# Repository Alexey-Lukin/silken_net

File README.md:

# 🌿 Silken Net

> ⚠️ **2026-11-22 — the project is being re-rooted.** The enzymatic fuel cell (EBFC) is cut from the product; hardware is to be designed for sampled «witness trees» rather than every tree, and a primary cell is now an allowed power source; the core product direction is an open radio dendrometer for research groups, with a second market and a sensor-agnostic node under study; the planned in-silico EBFC paper («Стаття 1») will not be published. Everything below still describes the previous design until it is rewritten. The verdicts live in [`docs/01_03_EBFC_Enzymatic_Bio_Fuel_Cell.md`](docs/01_03_EBFC_Enzymatic_Bio_Fuel_Cell.md) (§4, first paragraph), [`docs/00_01_Vision_Mission_and_Roadmap.md`](docs/00_01_Vision_Mission_and_Roadmap.md) (§2) and [`docs/00_02_Academic_Integration_and_IP.md`](docs/00_02_Academic_Integration_and_IP.md) (§2.1).

<!-- hero: one representative per macro-layer, bottom-up (tree → blockchain) -->
<p align="center">
  <a href="docs/01_03_EBFC_Enzymatic_Bio_Fuel_Cell.md">500mV in silico" src="https://img.shields.io/badge/EBFC%20%3E500mV%20in%20silico-2E7D32?style=flat-square"></a>

</p>

**Silken Net** is the world's first trustless **D-MRV** (Digital Measurement, Reporting & Verification) platform for planetary-scale forest-health monitoring. Each tree gets a machine identity (peaq DID), becomes an economic agent, and earns growth points that convert to **SCC** — computed from the node's wake interval (by design, its fuel cell's recharge time), a transitional rule until a separate growth witness exists; SCC is an internal accounting unit, not a registry carbon credit.

A titanium gyroid anchor carries an STM32 *Soldier* node whose power source is an open research bet — an enzymatic biofuel cell built into the anchor (EBFC, >500 mV computed in silico, not yet measured in a tree). The node senses → encrypts → transmits over LoRa 868 MHz to a *Queen* gateway, which relays via CoAP to a Rails 8 / PostgreSQL / Sidekiq backend and a 10-chain Web3 *Proof-of-Growth* pipeline.

> *"We do not merely watch the forest. We give it a digital will."*

**A note on language.** This README, [`CONTRIBUTING.md`](CONTRIBUTING.md) and [`SECURITY.md`](SECURITY.md) are in English; the `docs/` canon is written in Ukrainian, because it is where the engineering thinking actually happens and translating it would put a lossy layer between the author and the decisions. Issues and pull requests in English are welcome.

---

## 📚 Documentation

The canon lives in [`docs/`](docs/) as SSOT documents grouped into modules 00–06, and is mirrored to the GitHub wiki on every push to `main`.

> **Start at [`docs/00_00` — SSOT Index](docs/00_00_SSOT_Index.md):** reading order, the eight-layer system map, and a one-line description of every document. That index is the **single home of the list** — it is deliberately not restated here, so it cannot drift in two places.

- **Module 00 — foundation** (read first): vision and roadmap · AI-native method and NASA TRL · the TRL matrix with HIL simulators · the SSOT documentation standard · academic integration and the IP posture · Nature-as-a-Service contract terms · the beyond-TRL-9 agenda
- **Modules 01–06 — the system:** anchor and biofuel cell · capsule and gateway hardware (with the unit economics and BOM) · firmware and edge AI · the Rails core · Web3 and economics · deploy and observability

🔴 **Everything still unfinished — including the honest blockers — lives in [`docs/00_07` — Action Plan Tracker](docs/00_07_Action_Plan_Tracker.md).** It is a working document, not a highlight reel: open defects, refused proposals and named ceilings are in it on purpose.

---

## 🌍 The scale we build for

**One trillion trees.** Not "planetary" as a figure of speech — planetary as an order of magnitude: Earth carries roughly three trillion trees, and the design target is that any one of them can hold a machine identity, report on itself, and be paid for verified growth.

That number is a design constraint, not a boast. It is the denominator every architectural decision is divided by — RANGE-partitioned telemetry, strict-priority job queues, per-stream broadcast granularity, the bill of materials for a single node, the energy budget of a sensor that must run for two decades without a wire. A choice that is merely *fine* at ten thousand nodes and quietly quadratic at 10¹² is a defect here, even while it passes every test.

**And the honest half:** today the system stands at **TRL 3**, gated by the anchor and the biofuel cell — in-silico validated, not yet in-vitro; zero nodes in a forest. The trillion is what we are building *toward* and measuring *against*, never a claim about what runs today. This section is the public rendering; the canonical home of the constraint is [`docs/00_01 §1.1`](docs/00_01_Vision_Mission_and_Roadmap.md), which is where the rest of the canon cites the 10¹² denominator from. Current per-module readiness lives in [`docs/00_03 §1`](docs/00_03_TRL_Matrix_HIL_and_Beyond.md); the scaling phases and the beyond-TRL-9 agenda both in [`docs/00_01 §4`](docs/00_01_Vision_Mission_and_Roadmap.md).

---

## 🧬 Technology stack — a vertical cut through the trunk

_Bottom-up, the way sap climbs the xylem: from the root inside a living tree (**L1**) to finalisation on Ethereum (**L8**). What each layer means and what gates it — [`docs/00_00` § System Map](docs/00_00_SSOT_Index.md); the current readiness of each module — [`docs/00_03 §1`](docs/00_03_TRL_Matrix_HIL_and_Beyond.md), its single home, deliberately not restated here._

| Layer | Stack |
|:---|:---|
| **L1 · ROOT**<br><sub>Biophysics</sub> |         |
| **L2 · CAPSULE**<br><sub>Hardware</sub> |      |
| **L3 · BRAIN**<br><sub>Firmware + edge AI</sub> |        |
| **L4 · VESSELS**<br><sub>Network</sub> |     |
| **L5 · HEARTWOOD**<br><sub>Backend</sub> |             |
| ⛓ **L6 · CAMBIUM**<br><sub>Verification</sub> |      |
| ⛓ **L7 · CROWN**<br><sub>Finance</sub> |        |
| ⛓ **L8 · CANOPY TOP**<br><sub>Finalisation</sub> |     |
| 🌍 **SOIL**<br><sub>DevOps · CI · observability</sub> |                |

---

## 🚀 Quick start

### 0. System dependencies

Install these before `bundle install`.

**PostGIS** (required — cluster geometry lives in the database):

```bash
sudo apt-get install -y postgresql-17-postgis-3 postgresql-17-postgis-3-scripts   # Ubuntu / Debian
brew install postgis                                                             # macOS
```

The extension is enabled by `structure.sql` (`CREATE EXTENSION IF NOT EXISTS postgis`), so a normal `db:prepare` needs no manual step.

**A C toolchain** — several gems compile native extensions on install (e.g. `rbsecp256k1` builds libsecp256k1; `ed25519`, `keccak`, `oj`, `pg_query`, `puma`):

```bash
sudo apt-get install -y build-essential ruby-dev   # Ubuntu / Debian
xcode-select --install                             # macOS
```

### 1. Clone and set up

```bash
git clone https://github.com/Alexey-Lukin/silken_net.git
cd silken_net
bundle install
bin/rails db:prepare
```

### 2. Environment (`.env`)

```bash
cp .env.example .env
```

For local development and simulated telemetry most fields can stay empty — `REDIS_URL` (already in the template) and `WEB3_STRICT_MODE=false` are enough, the latter activating the Web3 stubs so no real keys are needed. Running the full Web3 stack (SCC minting, the Chainlink oracle, Solana micro-payments) needs real credentials; the inventory of which, and where each comes from, is [`docs/06_04` — Secrets Checklist](docs/06_04_Secrets_Checklist.md).

### 3. Run

```bash
bin/dev   # Rails + Sidekiq + Tailwind CSS + CoAP listener
```

### 4. Simulate telemetry (no physical hardware)

```bash
bin/rails runner "PartitionMaintenanceWorker.new.perform"   # partitions FIRST — see note
bin/rails db:seed      # Gateway, Tree, HardwareKey, TreeFamily
bin/forest_simulator   # CoAP packets from 5–15 Soldiers every 3–8 s
```

> **Why the worker runs first.** `db/seeds.rb` back-dates the "silent tree" to
> `73.hours.ago`, so on the 1st–3rd of a month that row targets the PREVIOUS month.
> `db/structure.sql` only carries the calendar frozen at dump time — if that month is
> missing, the row lands in the `_default` leaf silently and then blocks
> `CREATE … PARTITION OF` for it permanently (runbook `docs/06_06` §5.5). On
> `production` the seed refuses to run at all (slot guard; `00_07` OPS.38).

Watch the pipeline:

```bash
bin/rails runner "puts TelemetryLog.count"
open http://localhost:3000/sidekiq
tail -f log/development.log | grep -i telemetry
```

### 5. Tests and quality

```bash
bin/rspec                # full suite
bin/rubocop -a           # linter, safe autocorrect — run before every commit
bin/brakeman             # static security analysis
bin/bundler-audit check  # dependency advisories
```

Smart contracts (Foundry):

```bash
cd contracts
npm ci                           # OpenZeppelin + forge-std
forge build --sizes              # compile, report EIP-170 size
forge test -vvv --gas-report
forge coverage --report lcov     # ≥90% floor, enforced in CI
```

Suites live in `contracts/test/*.t.sol` — unit, symbolic proofs (Halmos + hevm), Medusa property fuzzing and Foundry stateful invariants. All of them gate merges into `main`.

### 6. Deploy (Kamal)

```bash
kamal setup
kamal deploy
```

> 🔏 **Signed releases.** The production image mirrored to GHCR carries a Sigstore-signed SLSA build-provenance attestation — verify it before pulling, per [`SECURITY.md`](SECURITY.md): `gh attestation verify oci://ghcr.io/alexey-lukin/silken_net:<tag> --owner Alexey-Lukin`.

---

## 🤝 Contributing

Bugs and proposals go through [GitHub Issues](https://github.com/Alexey-Lukin/silken_net/issues); vulnerabilities go **privately**, per [`SECURITY.md`](SECURITY.md) — please do not open a public issue for those. The contribution process (fork → branch → PR), the local checks to run before pushing, and the code requirements are in [`CONTRIBUTING.md`](CONTRIBUTING.md). Issues and pull requests in English are welcome even though the canon is Ukrainian.

---

## 📜 Licence and IP posture

SilkenNet is **mission-first and defensive-publication-first**: we deliberately **do not patent** this work. We publish it as prior art so that it stays free for every forest and **cannot be enclosed** by anyone — including us. The canonical statement of that posture is [`00_01 §8`](docs/00_01_Vision_Mission_and_Roadmap.md); the full map of zones and exceptions is [`NOTICE`](NOTICE).

| Zone | Licence | File |
|------|---------|------|
| **Code** (backend / firmware / tooling / IaC) | **GNU AGPL-3.0-or-later** — per-file SPDX | [`LICENSE`](LICENSE) |
| **Smart contracts** (`contracts/*.sol`) | **MIT** — per-file SPDX (on-chain composability and audit tooling) | [`LICENSE`](LICENSE) |
| **Hardware** (gyroid anchor / EBFC / PCB design) | **CERN-OHL-S-2.0** | [`LICENSE-HARDWARE.txt`](LICENSE-HARDWARE.txt) |
| **Documentation** (`docs/**`) | **CC-BY-SA-4.0** | [`LICENSE-DOCS.txt`](LICENSE-DOCS.txt) |

- **Patent non-assertion pledge.** We neither file nor assert patents; the inventive core is published as a defensive disclosure — [`docs/protocols/anchor/defensive_disclosure.md`](docs/protocols/anchor/defensive_disclosure.md).
- **Third-party exceptions.** AlphaFold 3 outputs (`docs/protocols/ebfc/in_silico/alphafold3/**` and `dgrGcGDH_AF3.pdb`) fall under AF3's own **non-commercial** Terms, **not** CC-BY-SA — see [`NOTICE`](NOTICE). The full dependency inventory is in `THIRD_PARTY_NOTICES`.
- **Trademarks.** SilkenNet™ / SCC™ are reserved for brand protection and are **not** licensed by any of the above.

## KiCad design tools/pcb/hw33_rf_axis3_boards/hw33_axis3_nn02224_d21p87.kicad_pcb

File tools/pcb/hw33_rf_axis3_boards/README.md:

# HW.33 — test boards of the RF mock-up, axis 3 (an antenna booster on a ground of our contour)

Axis 3 measures the efficiency of an antenna booster on a ground the size of the node's board — the number the ruling «for the small ground we pay in efficiency» stands on, and the one no evaluation board measures by construction ([`02_01 §5.3`](../../../docs/02_01_Hardware_Architecture_and_BOM.md); procedure — [`rf_mockup_bench_sheet`](../../../docs/protocols/hardware/rf_mockup_bench_sheet.md) §5). The sheet asks for two diameters — the sentinel Ø20.37 and Ø21.87 (in place of Ø19.37 since 2026-10-15: the root package of `02_01 §3.5` puts every board target with the clearance segment as a keep-out at or above Ø20.57) — and for both boosters that fit the contour where possible, so there are four boards. State and the order leg: [`00_07`](../../../docs/00_07_Action_Plan_Tracker.md) HW.33.

## What is here

| File | Role |
|---|---|
| `build_boards.py` | the source — generates everything below (AGPL-3.0-or-later, like all tooling); its header carries the vendor's footprint and evaluation-board numbers with the page each was read on, and every layout choice that is ours |
| `hw33_axis3_<booster>_d<Ø>.kicad_pcb` · `.kicad_pro` | the four boards and their design rules (KiCad 10) — `nn02224`/`nn02201` × `d20p37`/`d21p87` |
| `fab/<board>/gerbers/` | Gerber layers + Excellon drill, as text |
| `fab/<board>/<board>_bom.csv` | what goes on the board, for hand assembly |

The design outputs are hardware design and fall under **CERN-OHL-S-2.0** by the zone map in [`/NOTICE`](../../../NOTICE); KiCad's S-expressions have no comment syntax, so they carry no per-file tag.

Rebuild (KiCad 10 installed in `~/Applications/KiCad`):

```bash
~/Applications/KiCad/KiCad.app/Contents/Frameworks/Python.framework/Versions/3.9/bin/python3.9 -B \
    tools/pcb/hw33_rf_axis3_boards/build_boards.py
```

⛔ Keep `-B`: without it the interpreter writes `__pycache__/*.pyc` inside `KiCad.app`, which breaks the bundle's code signature (`codesign --verify --deep --strict` then reports «a sealed resource is missing or invalid»).

The run refuses a placement whose pads or booster body leave the contour, or a part that reaches into the clearance area; a board that fails DRC (any violation or unconnected item) is deleted with its project before any fabrication file is written; it also writes `fab/<board>/<board>_gerbers.zip` for the upload (ignored by git — it is rebuilt from the text gerbers).

## The boards

- **A disc of the contour, 2 layers, FR4 1.6 mm, ground poured on both layers and stitched.** The disc is the radiator: a booster excites the ground it sits on.
- **The booster at the top edge, in a clearance segment only 1.0 mm deeper than its pads.** The vendor's evaluation boards give the booster an 11 mm strip; ours is the narrowest the footprint allows, on purpose — the node's board budget has no room for a wide one, so the board measures what the product can have, and the number comes out more pessimistic than a wide clearance would give. Narrowest is not small: the segment over the chord is ≈ 26–30 % of the disc for `NN02-224` and ≈ 16–18 % for `NN02-201` (Ø21.87 · Ø20.37) — every run prints it in mm². The width is ratified (founder, 2026-10-12): the narrowest — grounds, price and weakest link in the bench sheet §5. Changing the strip is one constant in the generator, not a new design.
- **The feed:** a grounded coplanar line ≈ 51 Ω, then four 0603 sites — A shunt · B series · C shunt · D series (D fitted with 0 Ω) — and a U.FL. The VNA starts from the values of the smallest published ground for `NN02-224`, 40 × 20 — 27 nH · 8.2 nH · 2.0 pF ([`02_01 §5.3`](../../../docs/02_01_Hardware_Architecture_and_BOM.md)) — whose topology this pass did not see; the board takes a π (A B C) as well as a T (B C D). The vendor's ISM application note has six networks in our band, all read off their schematics: two L on 131 × 60 (863–870 MHz: 30 nH series + 20 nH shunt — B + C) and four T, among them the CR80 board's 863–870 MHz one (30 nH series · 13 nH shunt · 3 nH series — B · C · D) on a 75 × 54 ground, the smallest seen; not one is a π. The vendor's values are a starting point for the VNA, never ours.
- **Stitching:** a via 1.2 mm from each shunt's ground pad, one 1.2 mm from a ground pad of the U.FL (its other ground pad, against the clearance or the edge, has its nearest via 3.2–4.2 mm away on all four boards), a grid over the ground, and a fence along the line where the parts' pads leave room — at 868 MHz (λ_g ≈ 208 mm) every one of those spacings is far inside λ/20.
- **The mounting pad of the booster is left unconnected** — both manuals say it must not be grounded. The booster's body is placed as well as its pads: the `NN02-201` body (7.0 × 3.0) is wider than its pads, so it is the body that meets the contour.

## Ordering notes (👤)

1. **Order the boards bare** — nothing here needs a PCBA house: every matching part is chosen on the VNA, and the booster's two pads hand-solder.
2. **Parts:** the boosters `NN02-224` and `NN02-201` (from a distributor of Ignion), Hirose `U.FL-R-SMT-1`, a U.FL → SMA(F) **bulkhead** pigtail in **two lengths**, and a tuning set around the vendor's values in the parts the vendor itself names — Murata LQW18AN (0603) inductors, LQW15AN (0402) for the smallest ones, GJM1555 (0402) capacitors; a 0402 part sits on the 0603 sites by hand. Two lengths, because check (в) of the bench sheet's §5 (i) changes the cable length inside the cap, and a bulkhead pigtail lies wholly inside it, so one length cannot be changed; best of the same cable and connector, so that the check moves the length alone. The window puts the wall 86–105 mm from the DUT's centre and the U.FL (J1) sits 6.0–7.3 mm off that centre, so a pigtail of about 100 mm reaches the wall with slack only in the lower part of the window — the cap therefore belongs in the lower part of that window (a machine consequence; the cap's own window, inner Ø 172–210 mm, does not name it). The pair is TE Linx `CSH-SGFB-100-UFFR` (100 mm, two — one spare) and Taoglas `CAB.720` (200 mm overall) (⚖️ founder 2026-11-16, [`00_07`](../../../docs/00_07_Action_Plan_Tracker.md) HW.33 `Стан`); their cards give both a Ø1.32 cable, a U.FL plug and an SMA(F) bulkhead jack, so each swap remounts the bulkhead in the cap wall; the alternative named with it — a SMA F-F bulkhead in the wall with swappable cables — was not taken, nor was Taoglas `CAB.011` (IPEX MHF I, 95 mm of Ø1.13 cable). The set, as values (2026-10-18; five of each — four boards, swaps and hand-soldering losses):
   - inductors, LQW15AN (0402): 1.3 · 1.5 · 1.8 · 2.2 · 2.4 · 2.7 · 3.0 · 3.3 nH — Murata's part search (2026-11-16) finds no LQW15AN at 1.0 or 1.2 nH in any status, discontinued included, so by the rule below both became their nearest neighbour, 1.3, and the set lost one value; 1.8 nH is not in LQW15AN_80 and the search finds it in LQW15AN_00 (`LQW15AN1N8C00D`; its `…0Z` twins are the automotive grade), the rest in LQW15AN_80;
   - inductors, LQW18AN (0603): 3.9 · 4.7 · 5.6 · 6.8 · 7.5 · 8.2 · 8.7 · 10 · 12 · 13 · 15 · 18 · 20 · 22 · 24 · 27 · 30 · 33 · 39 · 47 · 56 · 68 nH;
   - capacitors, GJM1555 C0G (0402): 0.5 · 0.8 · 1.0 · 1.2 · 1.5 · 1.8 · 2.0 · 2.2 · 2.4 · 2.7 · 3.3 · 3.9 · 4.7 · 5.6 · 6.8 · 8.2 · 10 pF.

   Every value of the six application-note networks in the header of `build_boards.py`, filled out with E12 steps and two sub-1 pF trimmers (0.5 · 0.8 pF, not E12). The top of the inductor range is insurance, not a trend: our ground is smaller than every ground the vendor published a network for, and the vendor's own in-band series values do not grow as the ground shrinks (30 · 30 · 27 nH from 131 × 60 to 40 × 20), so the kit simply doubles the largest. Whether each value exists in its family is checked in Murata's own catalogue, with the vendor's own part numbers as positive controls — `LQW18AN30NG00` · `LQW18AN20NG00` · `LQW18AN13NG00` · `LQW15AN3N0B80D`; a value the family lacks (the smallest LQW15AN values are the likeliest) is replaced by its nearest neighbour. Checked 2026-11-16 against Murata's reference specifications `JELF243A-0024` (LQW18AN_00) and `JELF243A-0100` (LQW15AN_80) and its part search: every LQW18AN and GJM1555C1H value of the set exists (the LQW15AN gaps are in the row above). Below 10 nH the LQW18AN tolerance is a letter in nH — C ±0.2 or D ±0.5, and 4.7 nH comes only as D — so those order lines end `…C00D` / `…D00D`, never `…G00D`; in LQW15AN_80 the values up to 1.7 nH come only as C or D as well. Whether an order line is a part currently in production is read at order time.
3. **Clip ferrite chokes on the feeding cable** — on a ground of ≈ λ/16–17 (Ø21.87 · Ø20.37 against λ ≈ 345 mm at 868 MHz) the cable becomes part of the radiator, and without chokes the reading is optimistic (bench sheet §5). The Würth `74271111` named for this is rated for a 3.5–5 mm cable, so on the 1.32 mm coax it slides; no ready choke for a ≈ 1.3 mm cable with a vendor curve at 868 MHz turned up in one web search (2026-11-16), and a slip-on choke would have to pass the U.FL plug (the pigtail has connectors at both ends), so the clip stays and is held by tape stops on both sides — how, where, and the bench check of whether one pass is enough or two turns are needed, is step 3 of the bench sheet [`rf_mockup_bench_sheet`](../../../docs/protocols/hardware/rf_mockup_bench_sheet.md) §6 (the purchase verdict of 2026-11-16 did not judge the clip; [`00_07`](../../../docs/00_07_Action_Plan_Tracker.md) HW.33 `Стан`); it reopens only with Würth's safety key `74271`. Its own sheet rates it at 25 and 100 MHz only; read by eye off the steep fall of its typical curve (one turn), it gives roughly 290–350 Ω at 868 MHz — typical, not guaranteed.
4. The instruments of axis 3 — VNA, a closed Wheeler cap sized inside the window of the bench sheet's §5 (i) (not «≥ 55 mm and the bigger the safer»: a large cap is a cavity that resonates near our band), a step attenuator — are in the bench's instrument list; without them the boards wait.

> **Ordering codes — the suffix is the packaging, in the manufacturers' own sheets (2026-11-16):** `U.FL-R-SMT-1` is sold only with a packaging suffix — `U.FL-R-SMT-1(10)`, which Hirose's drawing of that part (`EDC3-302540-10`, marked «for reference», revision 2010) gives as a reel of 2,500 and distributors sell cut from it; `LQW18AN30NG00` is sold as `LQW18AN30NG00D`, where Murata's page gives the last letter as the package specification code and its reference specification `JELF243A-0024` reads D as taping (4,000 a reel) and B as bulk. The part numbers above stay as the design's; the suffix is the order line. Where it was read: the session handoff corpus — the distributors in `handoff/2026-11-15_hw9_hw33_purchase_submission.md`, the manufacturers' sheets in `handoff/2026-11-16_hw33_purchase_precheck.md`.

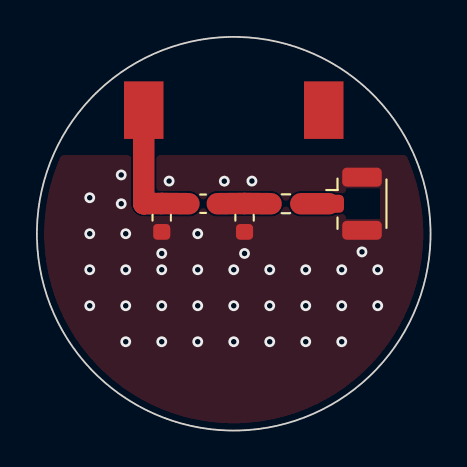
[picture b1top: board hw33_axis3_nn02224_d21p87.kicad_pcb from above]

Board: 2 copper layers, 21.9 x 21.9 mm, 6 parts (0 on the bottom side), 4 nets.

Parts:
A: DNP shunt; L_0603_1608Metric
AE1: NN02-224; Ignion_NN02-224
B: DNP series; L_0603_1608Metric
C: DNP shunt; L_0603_1608Metric
D: 0R series; R_0603_1608Metric
J1: U.FL-R-SMT-1; U.FL_Hirose_U.FL-R-SMT-1_Vertical

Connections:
ANT: A.1, AE1.1, B.1
GND: A.2, C.2, J1.2
N2: B.2, C.1, D.1
N3: D.2, J1.1
